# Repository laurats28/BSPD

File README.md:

# BSPD
Brake System Plausibity Devices

WIP

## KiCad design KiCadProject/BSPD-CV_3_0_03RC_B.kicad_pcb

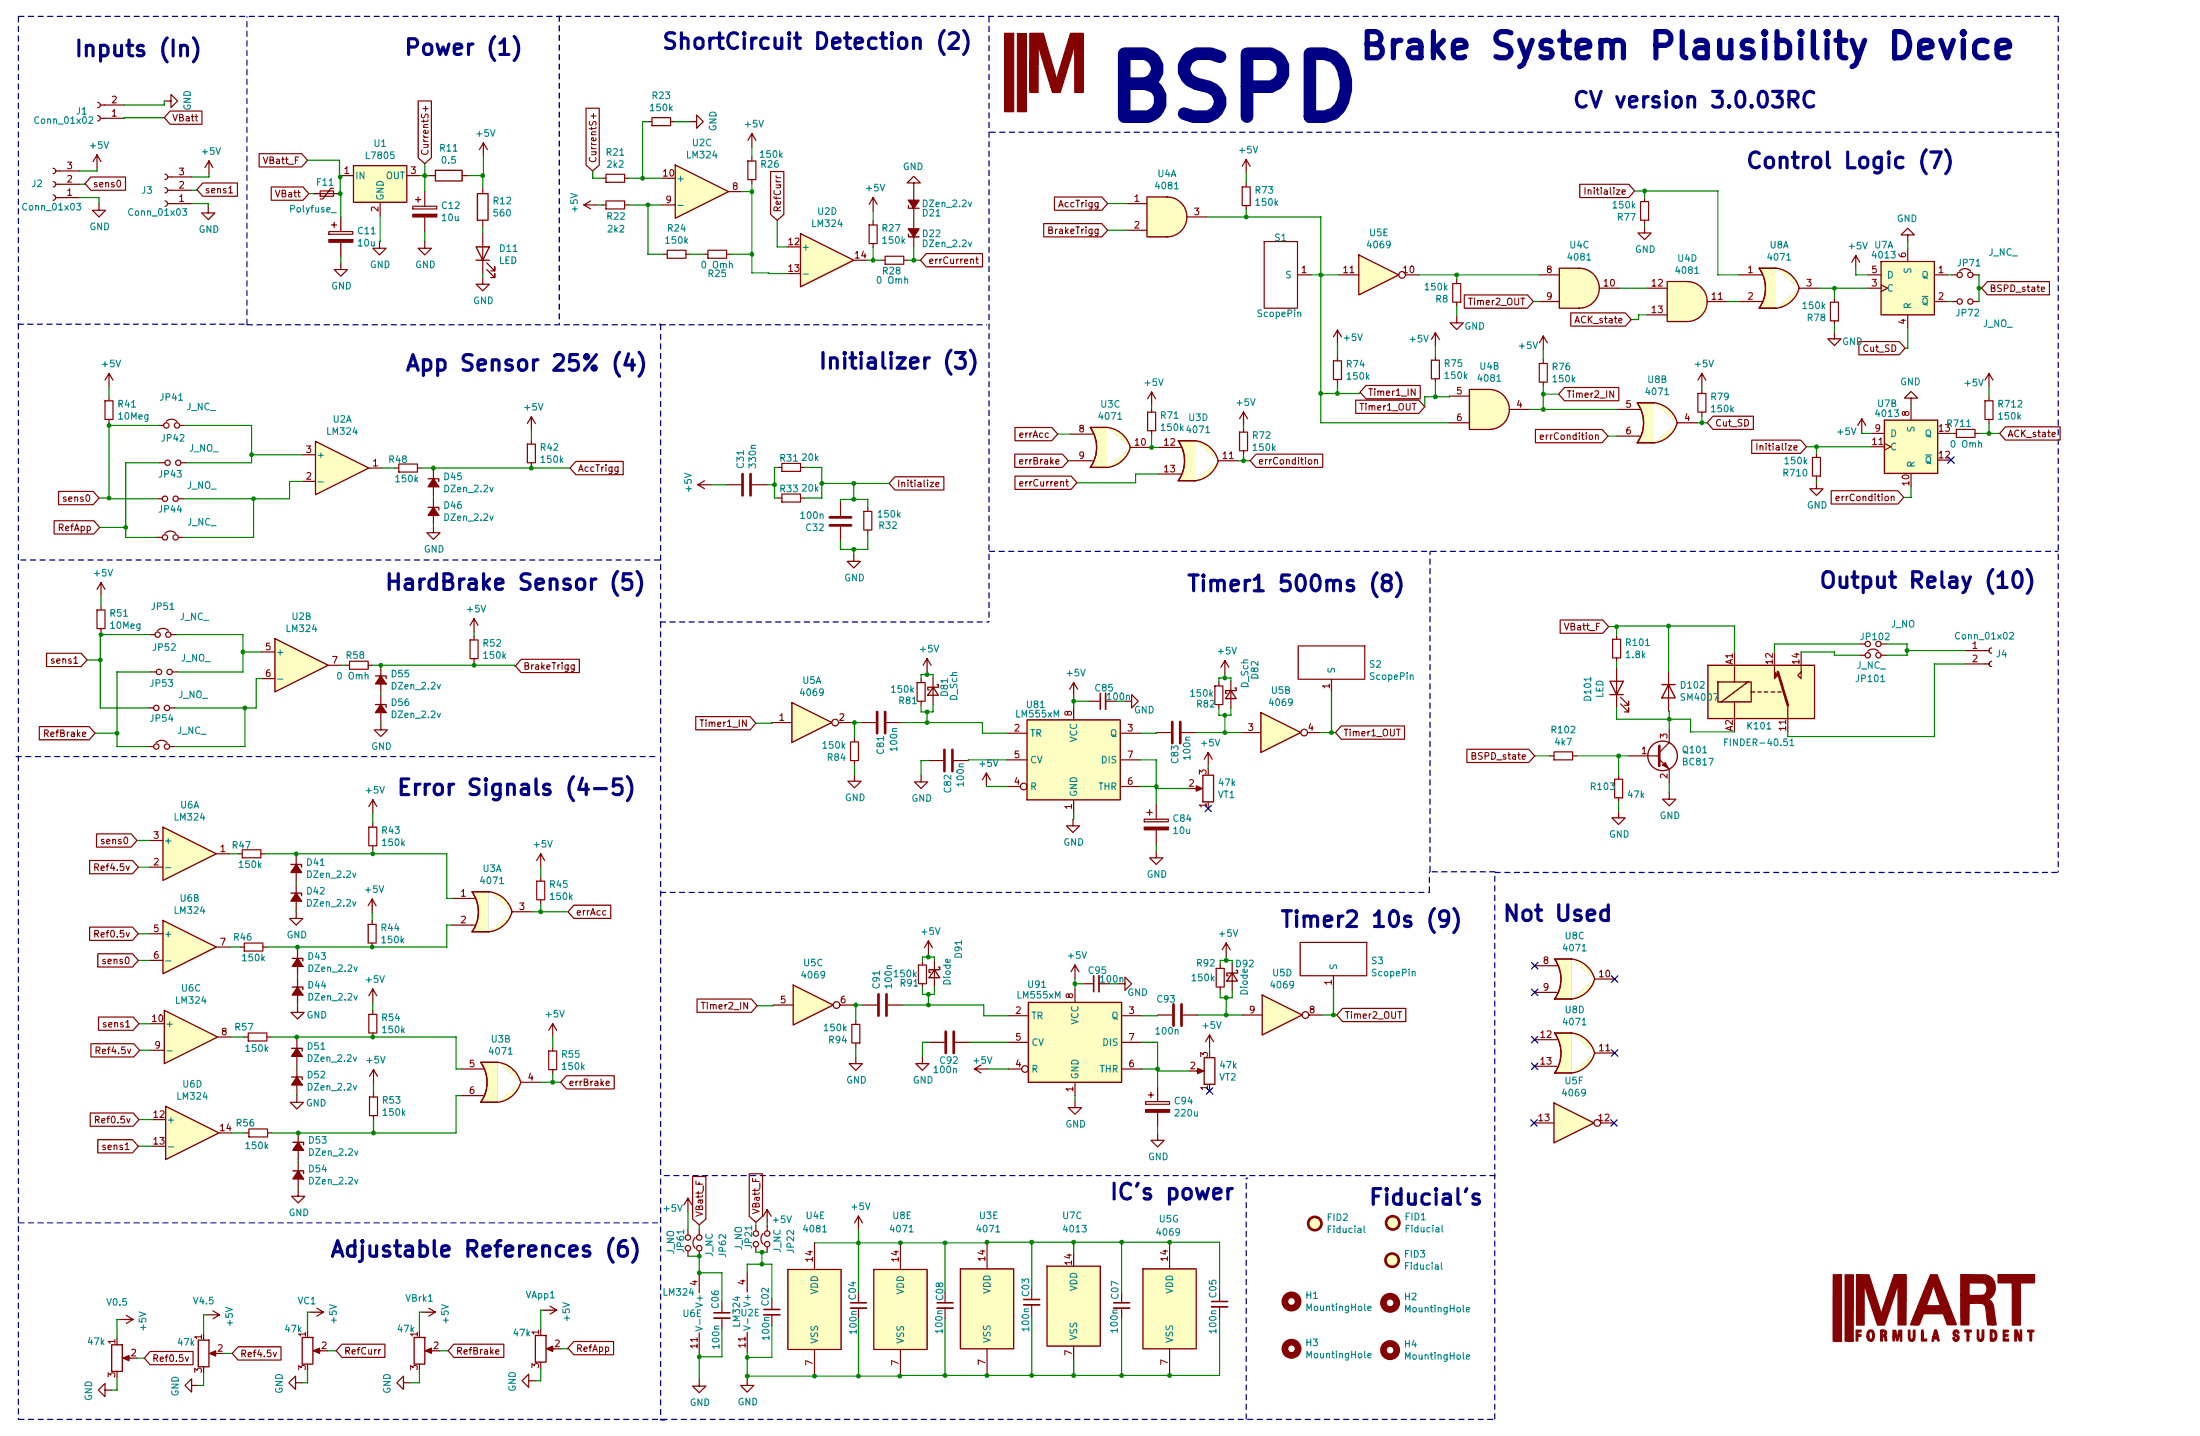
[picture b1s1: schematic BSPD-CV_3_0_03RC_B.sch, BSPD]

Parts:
C02, C03, C04, C05, C06, C07, C08, C32, C81, C82, C83, C85, C91, C92, C93, C95: 100n; C_0603_1608Metric_Pad1.08x0.95mm_HandSolder
C11, C12, C84: 10u; CP_Elec_4x5.3
C31: 330n; C_0603_1608Metric_Pad1.08x0.95mm_HandSolder
C94: 220u; CP_Elec_8x6.5
D11, D101: LED; LED_0603_1608Metric_Pad1.05x0.95mm_HandSolder
D21, D22, D41, D42, D43, D44, D45, D46, D51, D52, D53, D54, D55, D56: DZen_2.2v; D_DO-34_SOD68_P2.54mm_Vertical_AnodeUp
D81, D82: D_Sch; D_SOD-323F
D91, D92: Diode; D_SOD-323F
D102: SM4007; D_SOD-323F
F11: Polyfuse_; Fuse_1206_3216Metric_Pad1.42x1.75mm_HandSolder
FID1, FID2, FID3: Fiducial; Fiducial_0.5mm_Mask1.5mm
G2: LOGO; Logo_MART_40_40_2022
H1, H2, H3, H4: MountingHole; MountingHole_2.7mm_M2.5_DIN965_Pad
J1, J4: Conn_01x02; Molex_Nano-Fit_105313-xx02_1x02_P2.50mm_Horizontal
J2, J3: Conn_01x03; Molex_Nano-Fit_105313-xx03_1x03_P2.50mm_Horizontal
JP21, JP61, JP102: J_NO; SolderJumper-2_P1.3mm_Open_RoundedPad1.0x1.5mm
JP22, JP62: J_NC; SolderJumper-2_P1.3mm_Bridged_RoundedPad1.0x1.5mm
JP41, JP44, JP51, JP54, JP71, JP101: J_NC_; SolderJumper-2_P1.3mm_Bridged_RoundedPad1.0x1.5mm
JP42, JP43, JP52, JP53, JP72: J_NO_; SolderJumper-2_P1.3mm_Open_RoundedPad1.0x1.5mm
K101: FINDER-40.51; Rele 12VDC 5A Pan
Q101: BC817; SOT-23
R8, R23, R24, R26, R27, R32, R42, R43, R44, R45, R46, R47, R48, R52, R53, R54, R55, R56, R57, R71, R72, R73, R74, R75, R76, R77, R78, R79, R81, R82, R84, R91, R92, R94, R710, R712: 150k; R_0402_1005Metric_Pad0.72x0.64mm_HandSolder
R11: 0.5; R_1206_3216Metric_Pad1.30x1.75mm_HandSolder
R12: 560; R_0402_1005Metric_Pad0.72x0.64mm_HandSolder
R21, R22: 2k2; R_0402_1005Metric_Pad0.72x0.64mm_HandSolder
R25, R28, R58, R711: 0 Omh; R_0402_1005Metric_Pad0.72x0.64mm_HandSolder
R31, R33: 20k; R_0402_1005Metric_Pad0.72x0.64mm_HandSolder
R41, R51: 10Meg; R_0402_1005Metric_Pad0.72x0.64mm_HandSolder
R101: 1.8k; R_0402_1005Metric_Pad0.72x0.64mm_HandSolder
R102: 4k7; R_0402_1005Metric_Pad0.72x0.64mm_HandSolder
R103: 47k; R_0402_1005Metric_Pad0.72x0.64mm_HandSolder
S1, S2, S3: ScopePin
U1: L7805; SOT-223
U2, U6: LM324; SOIC-14_3.9x8.7mm_P1.27mm
U3, U8: 4071; SOIC-14_3.9x8.7mm_P1.27mm
U4: 4081; SOIC-14_3.9x8.7mm_P1.27mm
U5: 4069; SOIC-14_3.9x8.7mm_P1.27mm
U7: 4013; SOIC-14_3.9x8.7mm_P1.27mm
U81, U91: LM555xM; DIP-8_W7.62mm_Socket
V0.5, V4.5: 47k; RPot_6.71x7.04mm
VApp1: 47k; Potentiometer_Bourns_3214W_Vertical
VBrk1: 47k; Potentiometer_Bourns_3214W_Vertical
VC1: 47k; RPot_6.71x7.04mm
VT1, VT2: 47k; RPot_6.71x7.04mm

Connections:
+5V: C03.1, C04.1, C05.1, C07.1, C08.1, C31.1, C85.1, C95.1, D81.1 (K), D82.1 (K), D91.1 (K), D92.1 (K), J2.3, J3.3, JP22.2, JP61.2, R11.1, R12.1, R22.1, R26.1, R27.1, R41.1, R42.1, R43.1, R44.1, R45.1, R51.1, R52.1, R53.1, R54.1, R55.1, R71.1, R72.1, R73.1, R74.1, R75.1, R76.1, R79.1, R81.1, R82.1, R91.1, R92.1, R712.1, U3.14 (VDD), U4.14 (VDD), U5.14 (VDD), U7.5 (D), U7.9 (D), U7.14 (VDD), U8.14 (VDD), U81.4 (R), U81.8 (VCC), U91.4 (R), U91.8 (VCC), V0.5.1, V4.5.1, VApp1.1, VBrk1.1, VC1.1, VT1.3, VT2.3
ACK_state: R711.2, R712.2, U4.13
AccTrigg: D45.1 (K), D45.2 (A), D46.1 (K), R42.2, R48.2, U4.1
BSPD_state: JP71.2, JP72.2, R102.1
BrakeTrigg: D55.1 (K), R52.2, R58.2, U4.2
CurrentS+: C12.1, R11.2, R21.1, U1.3 (OUT)
Cut_SD: R79.2, U7.4 (R), U8.4
Initialize: C32.2, R31.2, R32.1, R33.2, R77.2, R710.2, U7.11 (C), U8.1
unnamed: C02.1, JP21.1, JP22.1, U2.4 (V+)
unnamed: C06.1, JP61.1, JP62.1, U6.4 (V+)
unnamed: C31.2, R31.1, R33.1
unnamed: C81.1, R84.2, U5.2
unnamed: C81.2, D81.2 (A), R81.2, U81.2 (TR)
unnamed: C82.2, U81.5 (CV)
unnamed: C83.1, U81.3 (Q)
unnamed: C83.2, D82.2 (A), R82.2, U5.3
unnamed: C84.1, U81.6 (THR), U81.7 (DIS), VT1.2
unnamed: C91.1, R94.2, U5.6
unnamed: C91.2, D91.2 (A), R91.2, U91.2 (TR)
unnamed: C92.2, U91.5 (CV)
unnamed: C93.1, U91.3 (Q)
unnamed: C93.2, D92.2 (A), R92.2, U5.9
unnamed: C94.1, U91.6 (THR), U91.7 (DIS), VT2.2
unnamed: D11.2 (A), R12.2
unnamed: D21.1 (K), D22.2 (A)
unnamed: D41.1 (K), R43.2, R47.2, U3.1
unnamed: D41.2 (A), D42.1 (K)
unnamed: D43.1 (K), R44.2, R46.2, U3.2
unnamed: D43.2 (A), D44.1 (K)
unnamed: D51.1 (K), R54.2, R57.2, U3.5
unnamed: D51.2 (A), D52.1 (K)
unnamed: D53.1 (K), R53.2, R56.2, U3.6
unnamed: D53.2 (A), D54.1 (K)
unnamed: D55.2 (A), D56.1 (K)
unnamed: D101.1 (K), D102.2 (A), K101.A2, Q101.3 (C)
unnamed: D101.2 (A), R101.2
unnamed: J4.1, JP101.2, JP102.2
unnamed: J4.2, K101.11
unnamed: JP41.2, JP42.2, U2.3 (+)
unnamed: JP43.2, JP44.2, U2.2 (-)
unnamed: JP51.2, JP52.2, U2.5 (+)
unnamed: JP53.2, JP54.2, U2.6 (-)
unnamed: JP71.1, U7.1 (Q)
unnamed: JP72.1, U7.2 (~Q)
unnamed: JP101.1, K101.14
unnamed: JP102.1, K101.12
unnamed: Q101.1 (B), R102.2, R103.2
unnamed: R8.2, U4.8, U5.10
unnamed: R21.2, R23.1, U2.10 (+)
unnamed: R22.2, R24.1, U2.9 (-)
unnamed: R24.2, R25.1
unnamed: R25.2, R26.2, U2.8, U2.13 (-)
unnamed: R27.2, R28.1, U2.14
unnamed: R46.1, U6.7
unnamed: R47.1, U6.1
unnamed: R48.1, U2.1
unnamed: R56.1, U6.14
unnamed: R57.1, U6.8
unnamed: R58.1, U2.7
unnamed: R71.2, U3.10, U3.12
unnamed: R78.2, U7.3 (C), U8.3
unnamed: R711.1, U7.13 (Q)
unnamed: U4.10, U4.12
unnamed: U4.11, U8.2
Ref0.5v: U6.5 (+), U6.12 (+), V0.5.2
Ref4.5v: U6.2 (-), U6.9 (-), V4.5.2
RefApp: JP42.1, JP44.1, VApp1.2
RefBrake: JP52.1, JP54.1, VBrk1.2
RefCurr: U2.12 (+), VC1.2
Timer1_IN: R73.2, R74.2, S1.1, U4.3, U4.6, U5.1, U5.11
Timer1_OUT: R75.2, S2.1, U4.5, U5.4
Timer2_IN: R76.2, U4.4, U5.5, U8.5
Timer2_OUT: S3.1, U4.9, U5.8
VBatt: F11.1, J1.1
VBatt_F: C11.1, D102.1 (K), F11.2, JP21.2, JP62.2, K101.A1, R101.1, U1.1 (IN)
errAcc: R45.2, U3.3, U3.8
errBrake: R55.2, U3.4, U3.9
errCondition: R72.2, U3.11, U7.10 (R), U8.6
errCurrent: D22.1 (K), R28.2, U3.13
sens0: J2.2, JP41.1, JP43.1, R41.2, U6.3 (+), U6.6 (-)
sens1: J3.2, JP51.1, JP53.1, R51.2, U6.10 (+), U6.13 (-)

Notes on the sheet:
BSPD
Inputs (In)
Power (1)
ShortCircuit Detection (2)
App Sensor 25% (4)
HardBrake Sensor (5)
Adjustable References (6)
IC's power
Timer2 10s (9)
Timer1 500ms (8)
Control Logic (7)
Output Relay (10)
Initializer (3)
Fiducial's
Brake System Plausibility Device
CV version 3.0.03RC
Not Used
Error Signals (4-5)

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
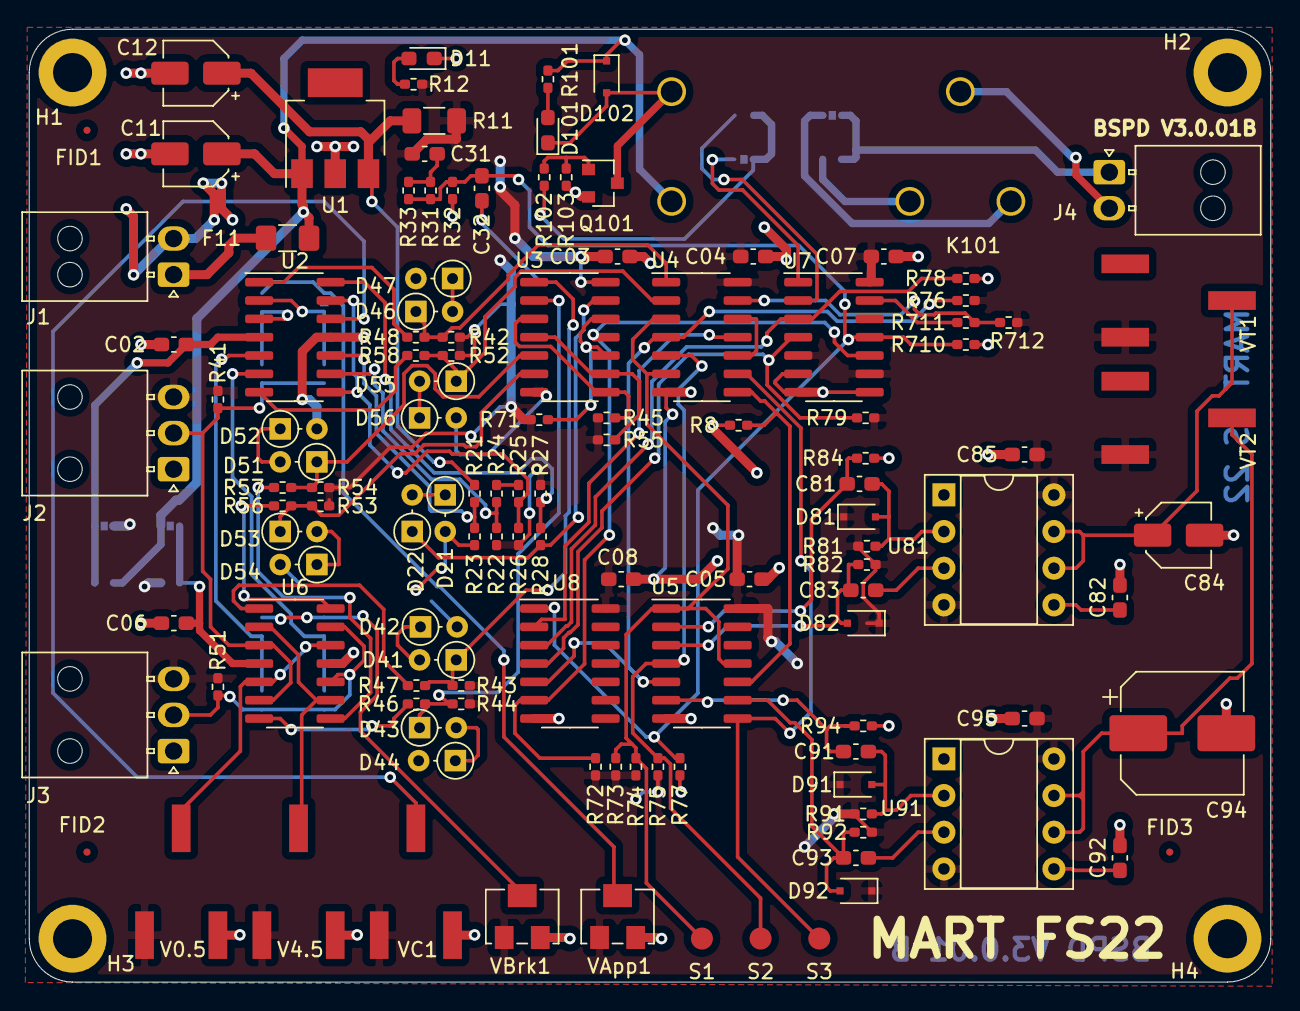
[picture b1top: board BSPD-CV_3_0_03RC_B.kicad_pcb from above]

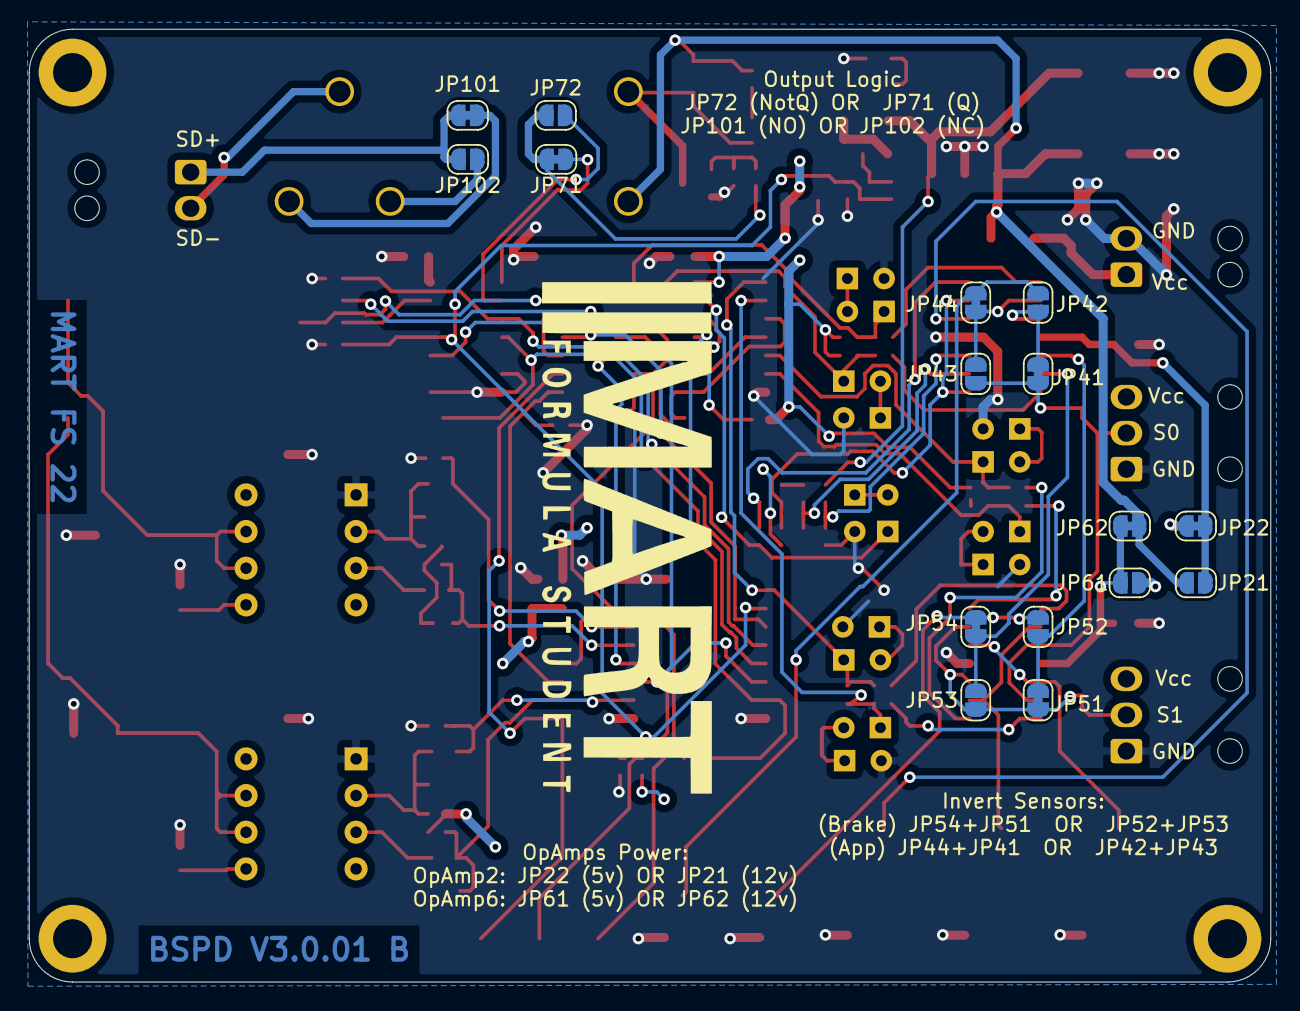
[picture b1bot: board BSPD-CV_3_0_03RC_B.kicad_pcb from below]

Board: 2 copper layers, 86.0 x 66.0 mm, 144 parts (17 on the bottom side), 83 nets.

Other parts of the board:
D47: DZen_2.2v; D_DO-34_SOD68_P2.54mm_Vertical_AnodeUp

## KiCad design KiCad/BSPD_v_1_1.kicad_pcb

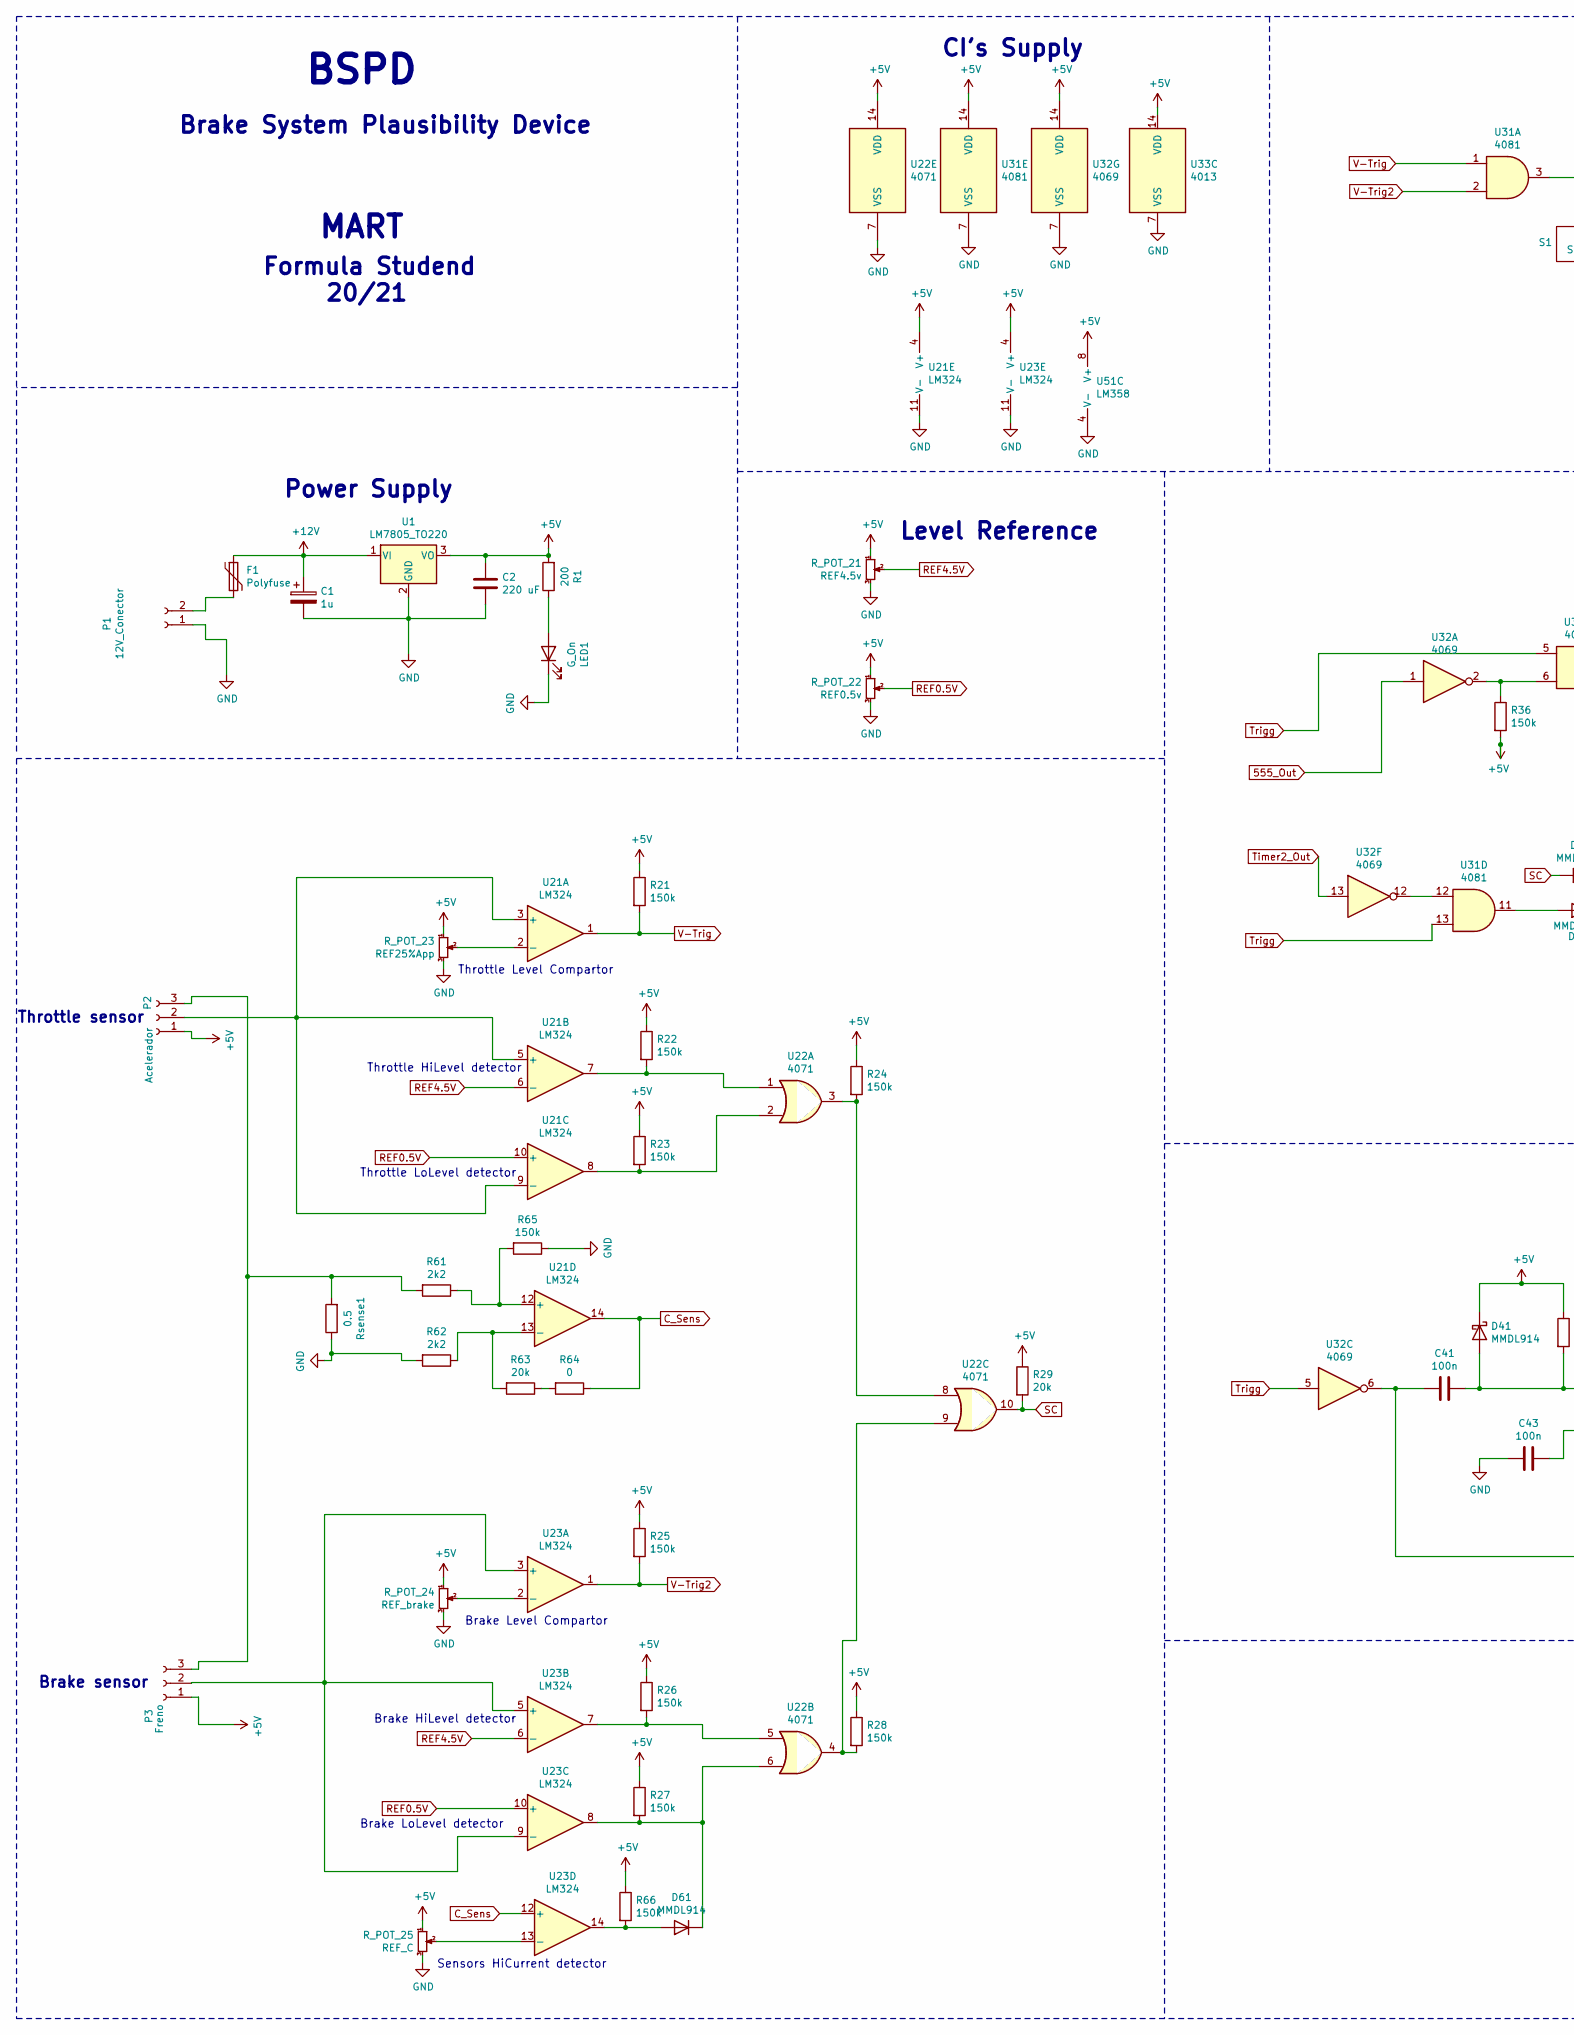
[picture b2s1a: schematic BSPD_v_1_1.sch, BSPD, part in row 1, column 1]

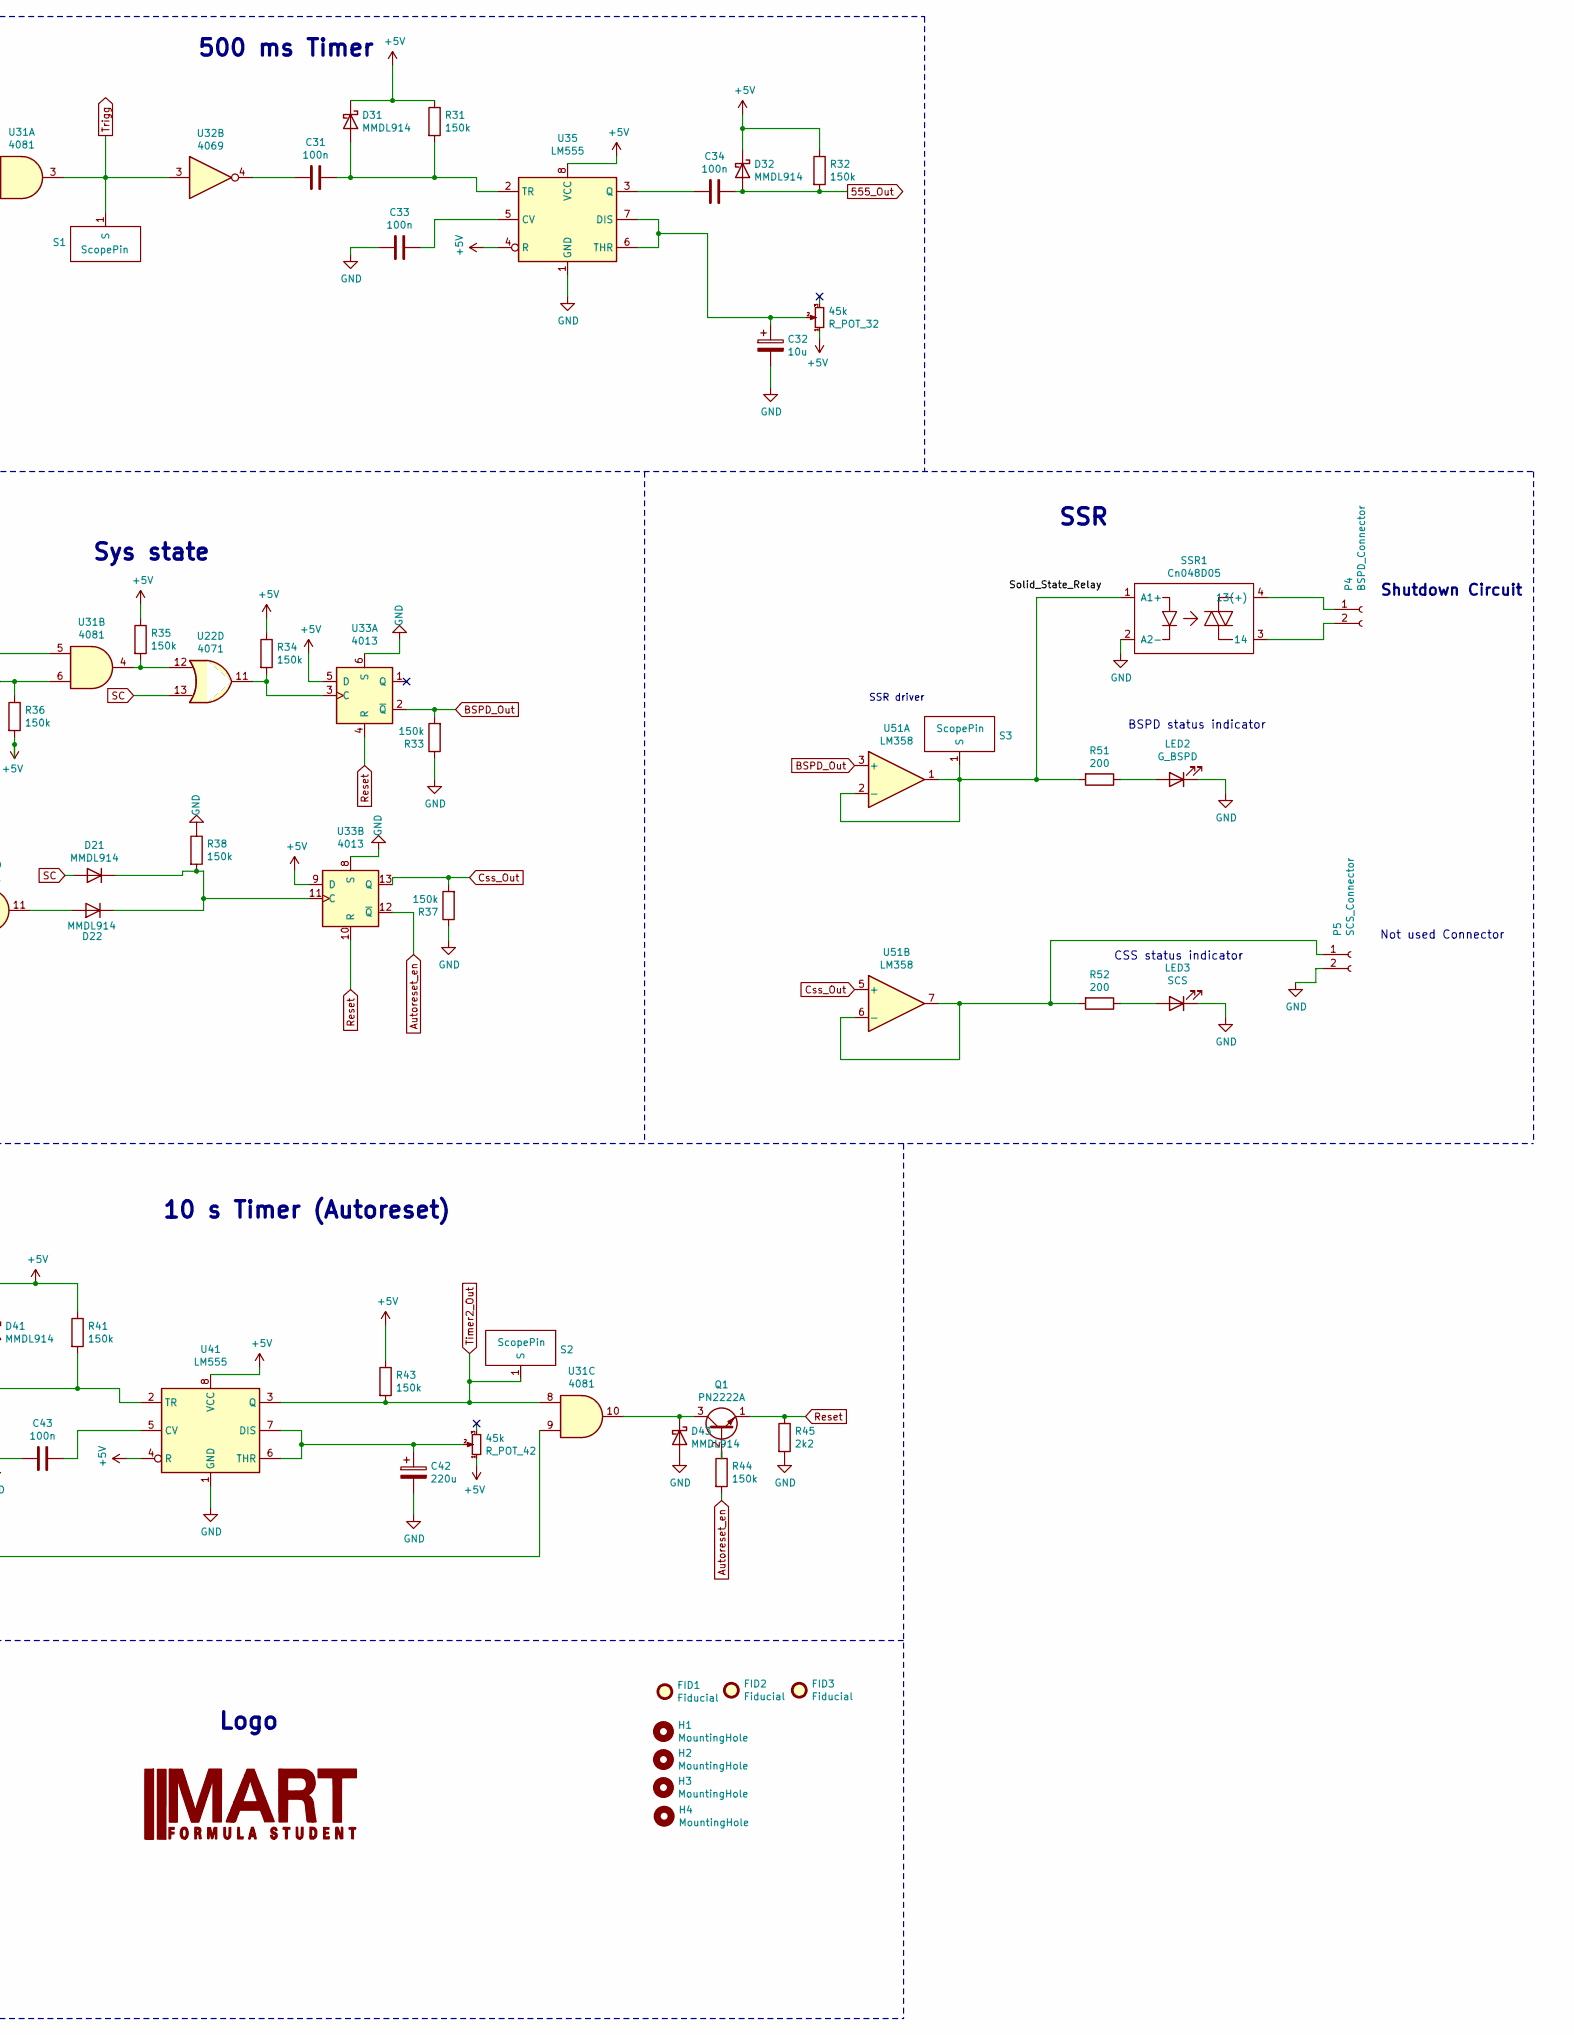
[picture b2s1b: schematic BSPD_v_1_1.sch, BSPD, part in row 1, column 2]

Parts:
C1: 1u; CP_Elec_4x5.4
C2: 220 uF; CP_Elec_6.3x7.7
C31, C33, C34, C41, C43: 100n; C_0805_2012Metric_Pad1.15x1.40mm_HandSolder
C32: 10u; CP_Elec_6.3x7.7
C42: 220u; CP_Elec_6.3x7.7
D21, D22, D31, D32, D41, D43, D61: MMDL914; D_SOD-323
F1: Polyfuse; Fuse_1206_3216Metric_Pad1.42x1.75mm_HandSolder
FID1, FID2, FID3: Fiducial; Fiducial_0.5mm_Mask1.5mm
H1, H2, H3, H4: MountingHole; MountingHole_2.7mm_M2.5
LED1: G_On; LED_0603_1608Metric_Pad1.05x0.95mm_HandSolder
LED2: G_BSPD; LED_0603_1608Metric_Pad1.05x0.95mm_HandSolder
LED3: SCS; LED_0603_1608Metric_Pad1.05x0.95mm_HandSolder
P1: 12V_Conector; Molex_Nano-Fit_105313-xx02_1x02_P2.50mm_Horizontal
P2: Acelerador; Molex_Nano-Fit_105313-xx03_1x03_P2.50mm_Horizontal
P3: Freno; Molex_Nano-Fit_105313-xx03_1x03_P2.50mm_Horizontal
P4: BSPD_Connector; Molex_Nano-Fit_105313-xx02_1x02_P2.50mm_Horizontal
P5: SCS_Connector; Molex_Nano-Fit_105313-xx02_1x02_P2.50mm_Horizontal
Q1: PN2222A; SOT-323_SC-70_Handsoldering
R1, R51, R52: 200; R_0603_1608Metric_Pad1.05x0.95mm_HandSolder
R21, R22, R23, R24, R25, R26, R27, R28, R31, R32, R33, R34, R35, R36, R37, R38, R41, R43, R44, R65, R66: 150k; R_0402_1005Metric
R29, R63: 20k; R_0402_1005Metric
R45, R61, R62: 2k2; R_0402_1005Metric
R64: 0; R_0402_1005Metric
R_POT_21: REF4.5v; Potentiometer_Bourns_3314J_Vertical
R_POT_22: REF0.5v; Potentiometer_Bourns_3314J_Vertical
R_POT_23: REF25%App; Potentiometer_Bourns_3224W_Vertical
R_POT_24: REF_brake; Potentiometer_Bourns_3224W_Vertical
R_POT_25: REF_C; Potentiometer_Bourns_3314J_Vertical
R_POT_32, R_POT_42: 45k; Potentiometer_Bourns_3314J_Vertical
Rsense1: 0.5; R_1206_3216Metric_Pad1.42x1.75mm_HandSolder
S1, S2, S3: ScopePin
SSR1: Cn048D05; Cn48D05
U1: LM7805_TO220; SOT-223
U21, U23: LM324; SOIC-14_3.9x8.7mm_P1.27mm
U22: 4071; SOIC-14_3.9x8.7mm_P1.27mm
U31: 4081; SOIC-14_3.9x8.7mm_P1.27mm
U32: 4069; SOIC-14_3.9x8.7mm_P1.27mm
U33: 4013; SOIC-14_3.9x8.7mm_P1.27mm
U35, U41: LM555; SOIC-8_3.9x4.9mm_P1.27mm
U51: LM358; SOIC-8_3.9x4.9mm_P1.27mm

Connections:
555_Out: C34.1, D32.2 (A), R32.2, U32.1
+5V: C2.1, D31.1 (K), D32.1 (K), D41.1 (K), P2.1, P3.1, R1.2, R21.1, R22.1, R23.1, R24.1, R25.1, R26.1, R27.1, R28.1, R29.1, R31.1, R32.1, R34.1, R35.1, R36.2, R41.1, R43.1, R66.1, R_POT_21.1, R_POT_22.1, R_POT_23.1, R_POT_24.1, R_POT_25.1, R_POT_32.1, R_POT_42.1, U1.3 (VO), U21.4 (V+), U22.14 (VDD), U23.4 (V+), U31.14 (VDD), U32.14 (VDD), U33.5 (D), U33.9 (D), U33.14 (VDD), U35.4 (R), U35.8 (VCC), U41.4 (R), U41.8 (VCC), U51.8 (V+)
+12V: C1.1, F1.1, U1.1 (VI)
Autoreset_en: R44.2, U33.12 (~Q)
BSPD_Out: R33.2, U33.2 (~Q), U51.3 (+)
C_Sens: R64.1, U21.14, U23.12 (+)
Css_Out: R37.2, U33.13 (Q), U51.5 (+)
GND: C1.2, C2.2, C32.2, C33.2, C42.2, C43.2, D43.2 (A), LED1.1 (K), LED2.1 (K), LED3.1 (K), P1.1, P5.2, R33.1, R37.1, R38.1, R45.2, R62.2, R65.1, R_POT_21.3, R_POT_22.3, R_POT_23.3, R_POT_24.3, R_POT_25.3, Rsense1.1, SSR1.2 (A2-), U1.2 (GND), U21.11 (V-), U22.7 (VSS), U23.11 (V-), U31.7 (VSS), U32.7 (VSS), U33.6 (S), U33.7 (VSS), U33.8 (S), U35.1 (GND), U41.1 (GND), U51.4 (V-)
unnamed: C31.1, D31.2 (A), R31.2, U35.2 (TR)
unnamed: C31.2, U32.4
unnamed: C32.1, R_POT_32.2, U35.6 (THR), U35.7 (DIS)
unnamed: C33.1, U35.5 (CV)
unnamed: C34.2, U35.3 (Q)
unnamed: C41.1, D41.2 (A), R41.2, U41.2 (TR)
unnamed: C41.2, U31.9, U32.6
unnamed: C42.1, R_POT_42.2, U41.6 (THR), U41.7 (DIS)
unnamed: C43.1, U41.5 (CV)
unnamed: D21.1 (K), D22.1 (K), R38.2, U33.11 (C)
unnamed: D22.2 (A), U31.11
unnamed: D43.1 (K), Q1.3 (C), U31.10
unnamed: D61.1 (K), R27.2, U22.6, U23.8
unnamed: D61.2 (A), R66.2, U23.14
unnamed: F1.2, P1.2
unnamed: LED1.2 (A), R1.1
unnamed: LED2.2 (A), R51.1
unnamed: LED3.2 (A), R52.1
unnamed: P2.2, U21.3 (+), U21.5 (+), U21.9 (-)
unnamed: P2.3, P3.3, R61.2, Rsense1.2
unnamed: P3.2, U23.3 (+), U23.5 (+), U23.9 (-)
unnamed: P4.1, SSR1.4 (13(+))
unnamed: P4.2, SSR1.3 (14)
unnamed: P5.1, R52.2, U51.6 (-), U51.7
unnamed: Q1.2 (B), R44.1
unnamed: R22.2, U21.7, U22.1
unnamed: R23.2, U21.8, U22.2
unnamed: R24.2, U22.3, U22.8
unnamed: R26.2, U22.5, U23.7
unnamed: R28.2, U22.4, U22.9
unnamed: R34.2, U22.11, U33.3 (C)
unnamed: R35.2, U22.12, U31.4
unnamed: R36.1, U31.6, U32.2
unnamed: R51.2, S3.1, SSR1.1 (A1+), U51.1, U51.2 (-)
unnamed: R61.1, R65.2, U21.12 (+)
unnamed: R62.1, R63.2, U21.13 (-)
unnamed: R63.1, R64.2
unnamed: R_POT_23.2, U21.2 (-)
unnamed: R_POT_24.2, U23.2 (-)
unnamed: R_POT_25.2, U23.13 (-)
unnamed: U31.12, U32.12
REF0.5V: R_POT_22.2, U21.10 (+), U23.10 (+)
REF4.5V: R_POT_21.2, U21.6 (-), U23.6 (-)
Reset: Q1.1 (E), R45.1, U33.4 (R), U33.10 (R)
SC: D21.2 (A), R29.2, U22.10, U22.13
Timer2_Out: R43.2, S2.1, U31.8, U32.13, U41.3 (Q)
Trigg: S1.1, U31.3, U31.5, U31.13, U32.3, U32.5
V-Trig: R21.2, U21.1, U31.1
V-Trig2: R25.2, U23.1, U31.2

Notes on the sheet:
Throttle sensor
Level Reference
Power Supply
Brake sensor
500 ms Timer
10 s Timer (Autoreset)
Sys state
SSR driver
SSR
Shutdown Circuit
BSPD status indicator
CSS status indicator
Not used Connector
Throttle HiLevel detector
Throttle LoLevel detector
Throttle Level Compartor
Brake Level Compartor
Brake HiLevel detector
Brake LoLevel detector
Sensors HiCurrent detector
CI's Supply
BSPD
Brake System Plausibility Device
Formula Studend 20/21
MART
Logo

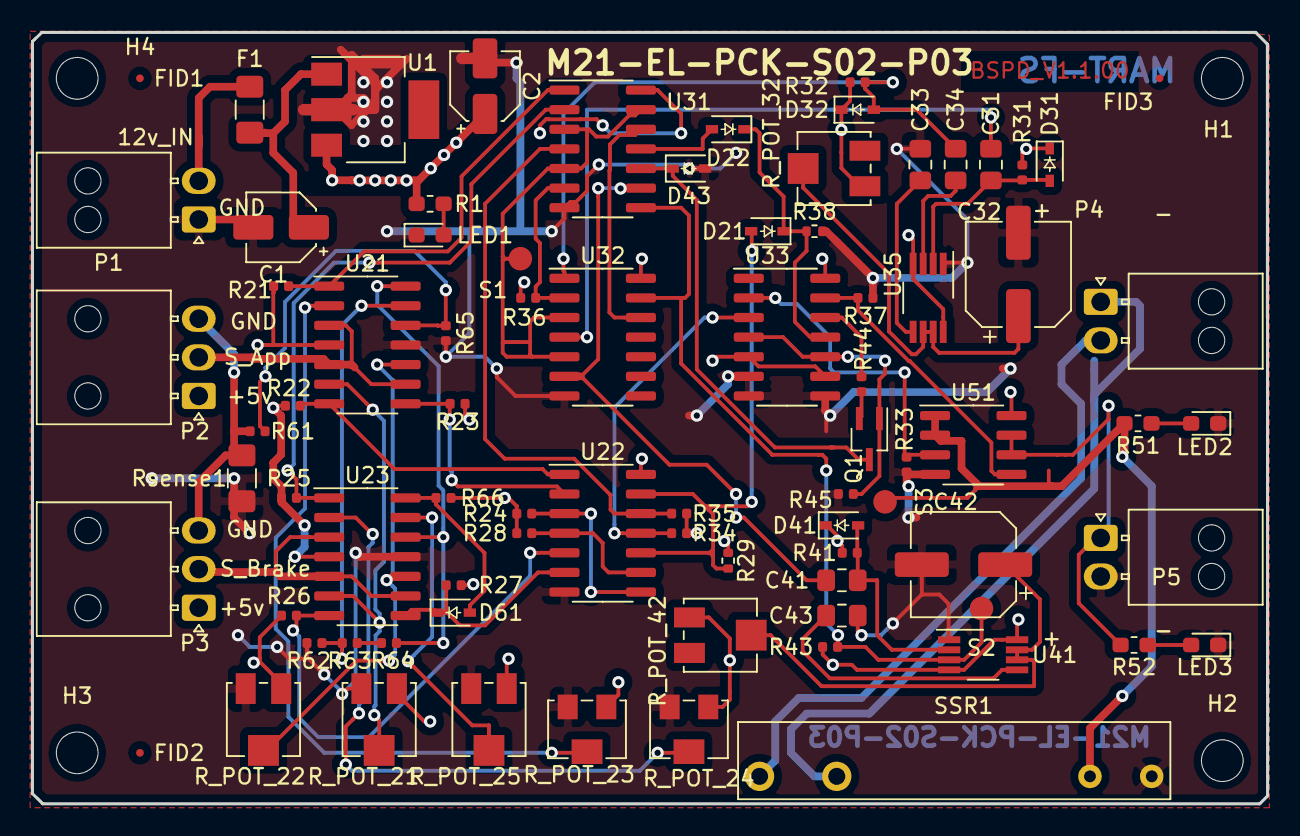
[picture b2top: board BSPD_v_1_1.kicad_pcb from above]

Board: 2 copper layers, 80.0 x 50.0 mm, 85 parts (0 on the bottom side), 57 nets.

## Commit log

2021-06-11 Add Gerbers Files
2021-06-11 Add BSPD Schematic
2021-06-11 Add Images
2021-06-11 Add KiCad Project
2021-06-11 Add MART Lbrary Symbols
2021-06-28 Add V1_1_00 version of BSPD
    BugFixes from v1_0_00
2021-07-31 .ino for nano to read the time taken by the BSPD
2022-05-10 Gerber Files
2022-05-10 PCBSizesSchematic
2022-05-11 Gerbers V3.0.03RC
    Gerbers Ordered To JLCPCB
2022-05-11 Schematic V3.0.03RC
2022-05-11 Add KiCad Project + Photos V3.0.03RC
2023-03-06 V4.0.0
2023-03-06 Gerbers2023
